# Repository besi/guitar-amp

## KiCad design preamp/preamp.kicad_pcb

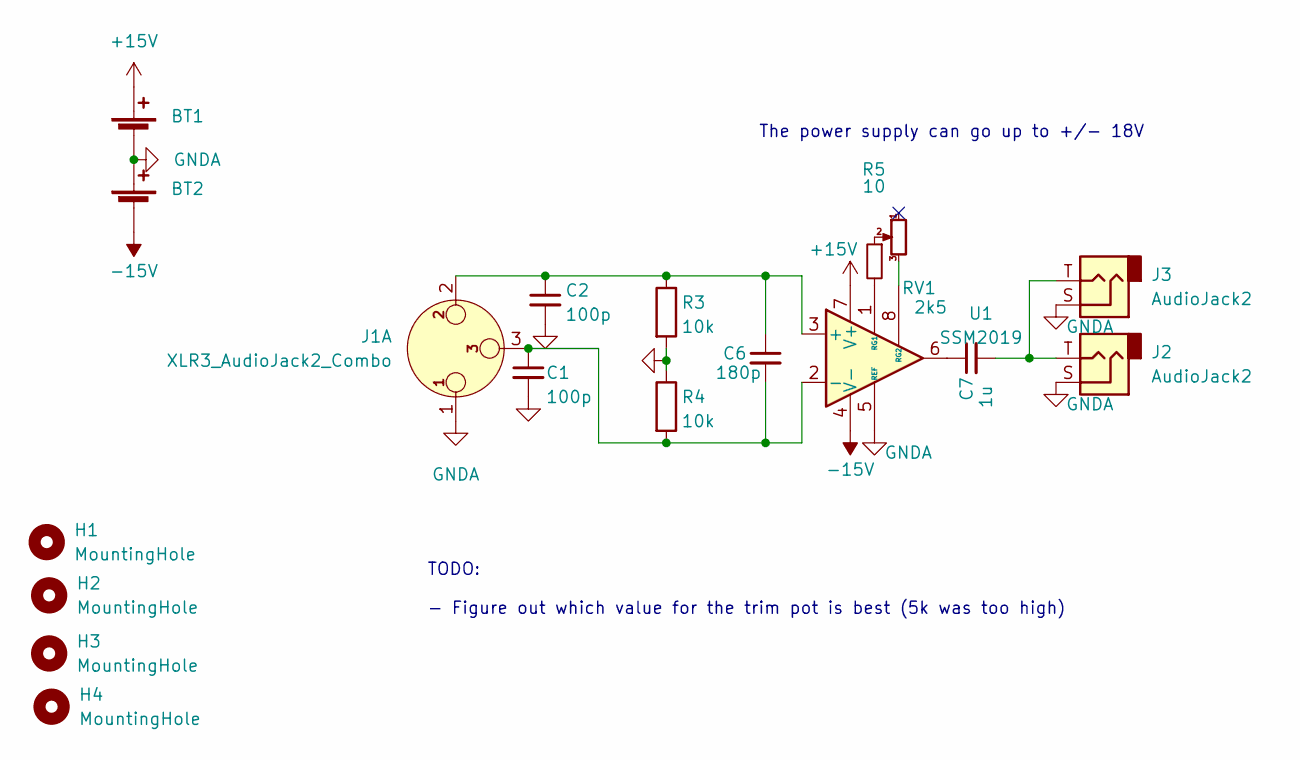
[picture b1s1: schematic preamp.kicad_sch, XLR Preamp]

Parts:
BT1, BT2: Battery_Cell; BarrelJack_GCT_DCJ200-10-A_Horizontal
C1, C2: 100p; C_Disc_D3.0mm_W1.6mm_P2.50mm
C6: 180p; C_Disc_D3.0mm_W1.6mm_P2.50mm
C7: 1u; C_Rect_L7.0mm_W2.5mm_P5.00mm
H1, H2, H3, H4: MountingHole; MountingHole_3.2mm_M3_DIN965
J1: XLR3_AudioJack2_Combo; Jack_XLR_Neutrik_NC3FAAH2_Horizontal
J2: AudioJack2; Jack_6.35mm_Neutrik_NMJ6HFD2_Horizontal
J3: AudioJack2; Jack_3.5mm_CUI_SJ-3523-SMT_Horizontal
R3, R4: 10k; R_Axial_DIN0207_L6.3mm_D2.5mm_P7.62mm_Horizontal
R5: 10; R_Axial_DIN0207_L6.3mm_D2.5mm_P7.62mm_Horizontal
RV1: 2k5; Potentiometer_Alps_RK163_Single_Horizontal
U1: SSM2019; DIP-8_W7.62mm_LongPads

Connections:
+15V: BT1.1 (+), U1.7 (V+)
-15V: BT2.2 (-), U1.4 (V-)
GNDA: BT1.2 (-), BT2.1 (+), C1.2, C2.2, J1.1, J2.S, J3.S, R3.2, R4.1, U1.5 (REF)
unnamed: C1.1, C6.2, J1.3, R4.2, U1.2 (-)
unnamed: C2.1, C6.1, J1.2, R3.1, U1.3 (+)
unnamed: C7.1, U1.6
unnamed: C7.2, J2.T, J3.T
unnamed: R5.1, RV1.2
unnamed: R5.2, U1.1 (RG1)
unnamed: RV1.3, U1.8 (RG2)

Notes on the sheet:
The power supply can go up to +/- 18V
TODO: - Figure out which value for the trim pot is best (5k was too high)

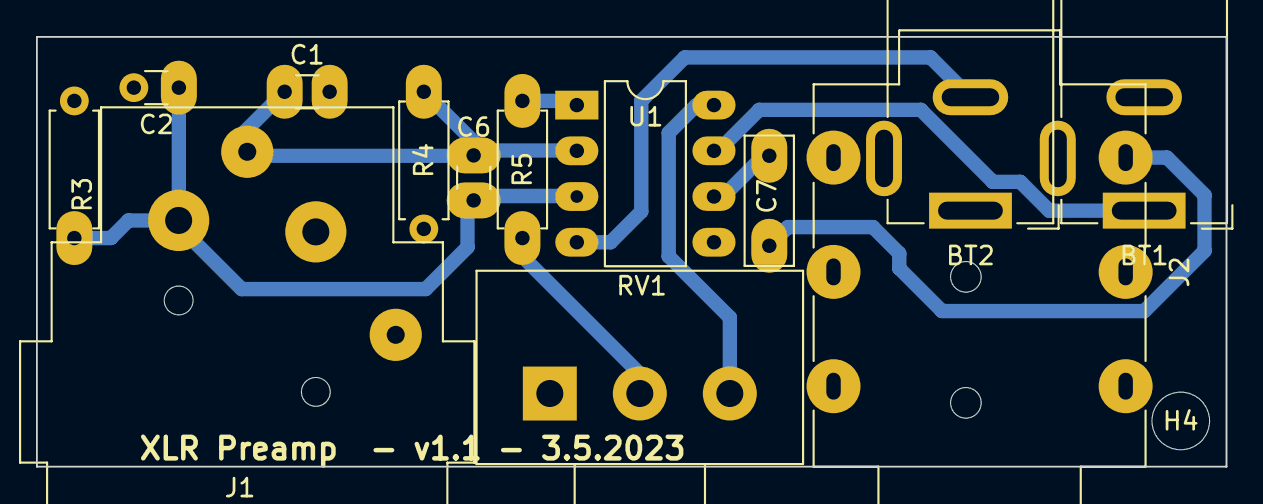
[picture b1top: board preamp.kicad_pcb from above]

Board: 2 copper layers, 66.1 x 23.9 mm, 18 parts (1 on the bottom side), 10 nets.

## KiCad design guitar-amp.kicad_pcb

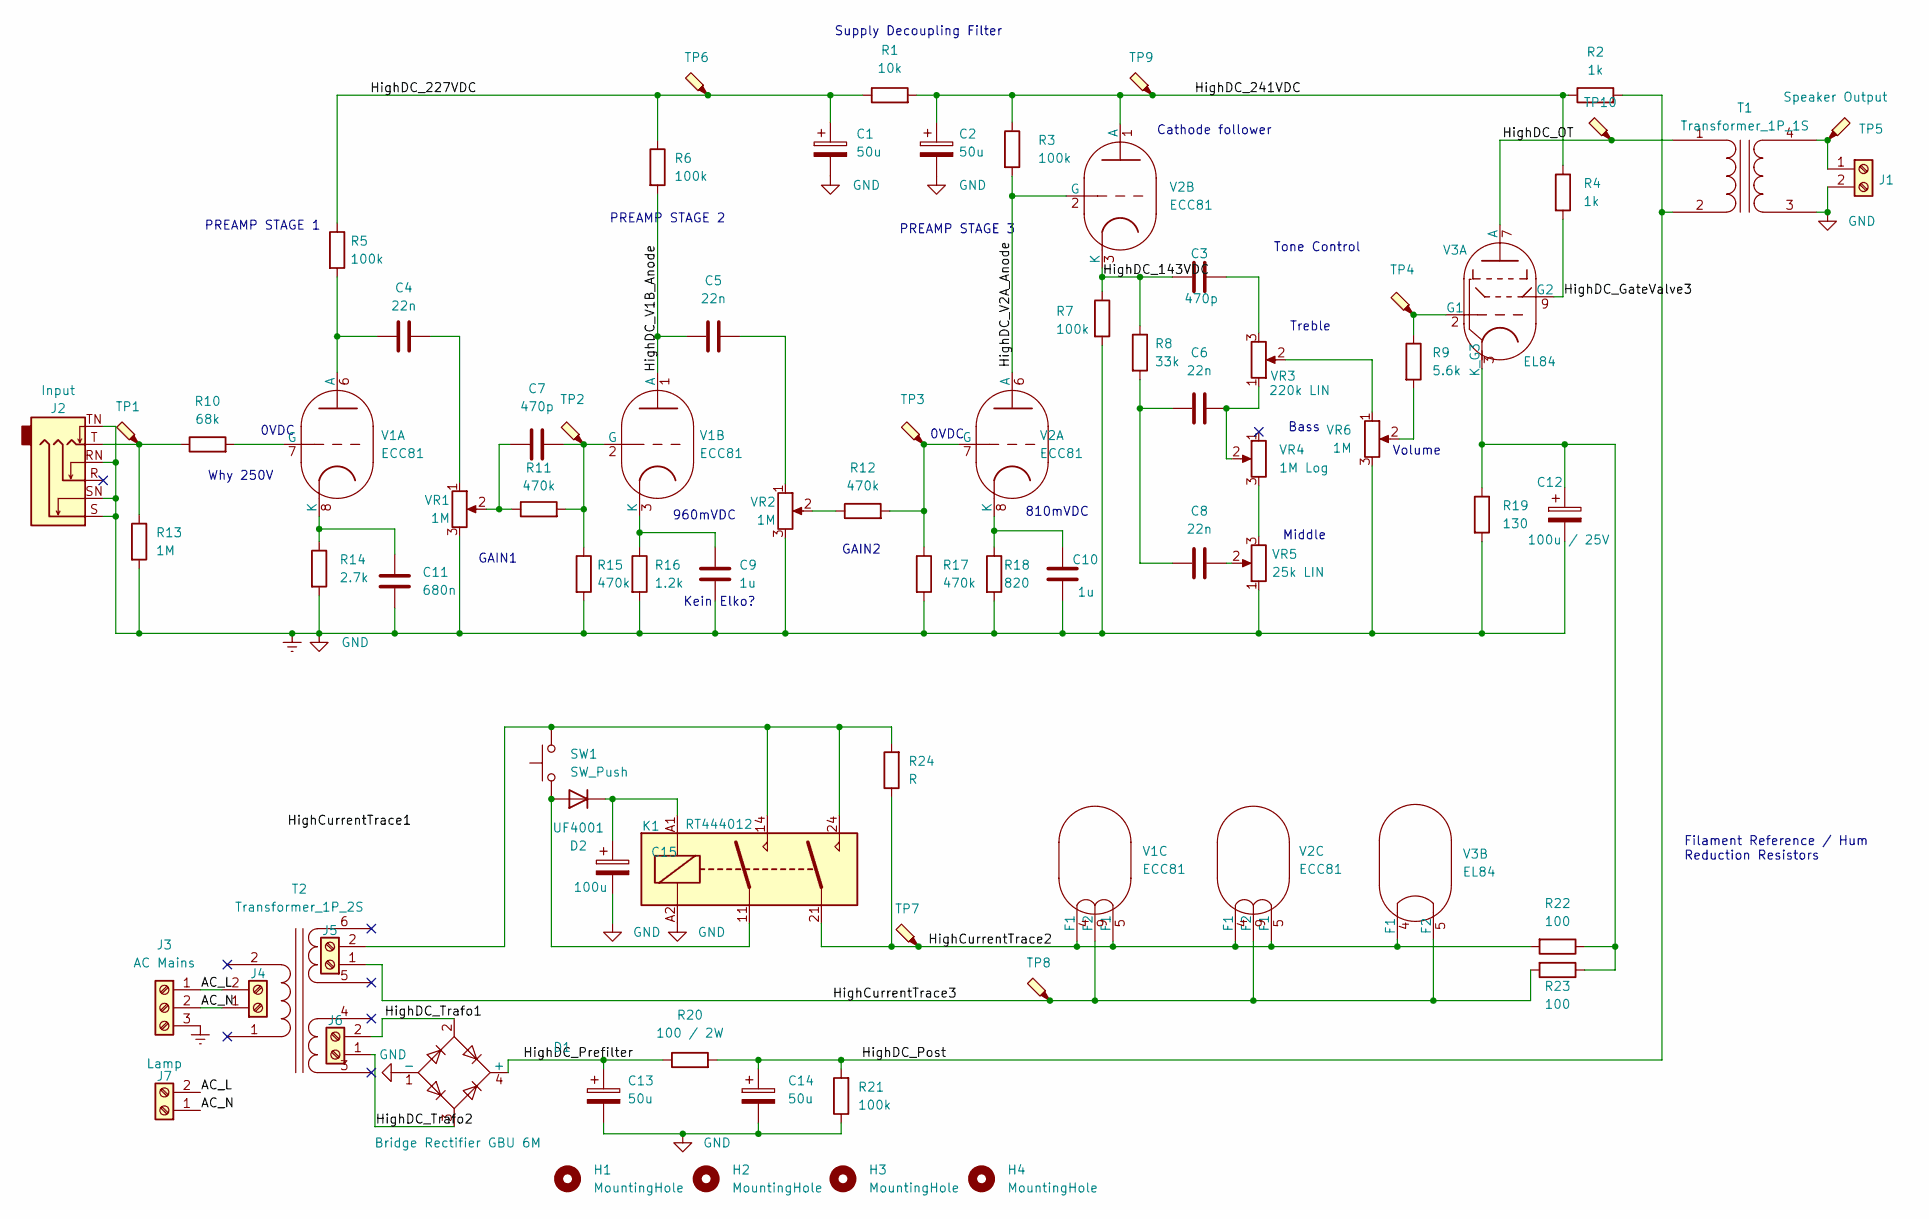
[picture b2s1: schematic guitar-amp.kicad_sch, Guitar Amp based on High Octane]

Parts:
C1, C2, C13, C14: 50u; CP_Radial_D16.0mm_P7.50mm
C3, C7: 470p; C_Disc_D7.0mm_W2.5mm_P5.00mm
C4, C5, C6, C8: 22n; C_Rect_L18.0mm_W5.0mm_P15.00mm_FKS3_FKP3
C9, C10: 1u; C_Rect_L10.3mm_W5.0mm_P7.50mm_MKS4
C11: 680n; C_Axial_L17.0mm_D7.0mm_P20.00mm_Horizontal
C12: 100u / 25V; CP_Radial_D8.0mm_P3.80mm
C15: 100u
D1: Bridge Rectifier GBU 6M; Diode_Bridge_Vishay_GBU
D2: UF4001; D_DO-41_SOD81_P10.16mm_Horizontal
H1, H2, H3, H4: MountingHole; MountingHole_3.2mm_M3
J1: Speaker Output; TerminalBlock_RND_205-00001_1x02_P5.00mm_Horizontal
J2: Input; Jack_6.35mm_Neutrik_NMJ6HFD2-AU_Horizontal
J3: AC Mains; TerminalBlock_RND_205-00002_1x03_P5.00mm_Horizontal
J4, J5, J6: Screw_Terminal_01x02; TerminalBlock_RND_205-00001_1x02_P5.00mm_Horizontal
J7: Lamp; TerminalBlock_RND_205-00001_1x02_P5.00mm_Horizontal
K1: RT444012; Relay_DPST_Schrack-RT2-FormA_RM5mm
R1: 10k; R_Axial_DIN0411_L9.9mm_D3.6mm_P12.70mm_Horizontal
R2, R4: 1k; R_Axial_DIN0411_L9.9mm_D3.6mm_P12.70mm_Horizontal
R3, R5, R6, R7: 100k; R_Axial_DIN0207_L6.3mm_D2.5mm_P7.62mm_Horizontal
R8: 33k; R_Axial_DIN0207_L6.3mm_D2.5mm_P7.62mm_Horizontal
R9: 5.6k; R_Axial_DIN0207_L6.3mm_D2.5mm_P7.62mm_Horizontal
R10: 68k; R_Axial_DIN0207_L6.3mm_D2.5mm_P7.62mm_Horizontal
R11, R12, R15, R17: 470k; R_Axial_DIN0207_L6.3mm_D2.5mm_P7.62mm_Horizontal
R13: 1M; R_Axial_DIN0207_L6.3mm_D2.5mm_P7.62mm_Horizontal
R14: 2.7k; R_Axial_DIN0207_L6.3mm_D2.5mm_P7.62mm_Horizontal
R16: 1.2k; R_Axial_DIN0207_L6.3mm_D2.5mm_P7.62mm_Horizontal
R18: 820; R_Axial_DIN0207_L6.3mm_D2.5mm_P7.62mm_Horizontal
R19: 130; R_Axial_DIN0411_L9.9mm_D3.6mm_P12.70mm_Horizontal
R20: 100 / 2W; R_Axial_DIN0411_L9.9mm_D3.6mm_P12.70mm_Horizontal
R21: 100k; R_Axial_DIN0411_L9.9mm_D3.6mm_P12.70mm_Horizontal
R22, R23: 100; R_Axial_DIN0207_L6.3mm_D2.5mm_P7.62mm_Horizontal
R24: R; R_Axial_Power_L20.0mm_W6.4mm_P25.40mm
SW1: SW_Push; SW_Tactile_SPST_Angled_PTS645Vx58-2LFS
T1: Transformer_1P_1S; TerminalBlock_RND_205-00003_1x04_P5.00mm_Horizontal
T2: Transformer_1P_2S
TP1, TP2, TP3, TP4, TP5, TP6, TP7, TP8, TP9, TP10: TestPoint_Probe; TestPoint_Pad_D2.5mm
V1, V2: ECC81; Valve_ECC-83-1
V3: EL84; Valve_ECC-83-1
VR1, VR2, VR6: 1M; Potentiometer_Alps_RK163_Single_Horizontal
VR3: 220k LIN; Potentiometer_Alps_RK163_Single_Horizontal
VR4: 1M Log; Potentiometer_Alps_RK163_Single_Horizontal
VR5: 25k LIN; Potentiometer_Alps_RK163_Single_Horizontal

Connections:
/AC_L: J3.1, J4.2, J7.2
/AC_N: J3.2, J4.1, J7.1
/HighCurrentTrace2: K1.21, R22.2, R24.1, TP7.1, V1.4 (F1), V1.5 (F1), V2.4 (F1), V2.5 (F1), V3.4 (F1)
/HighCurrentTrace3: J5.1, R23.2, TP8.1, V1.9 (F2), V2.9 (F2), V3.5 (F2)
/HighDC_143VDC: C3.1, R7.1, R8.1, V2.3 (K)
/HighDC_227VDC: C1.1, R1.1, R5.1, R6.1, TP6.1
/HighDC_241VDC: C2.1, R1.2, R2.1, R3.1, R4.1, TP9.1, V2.1 (A)
/HighDC_GateValve3: R4.2, V3.9 (G2)
/HighDC_OT: T1.1 (AA), TP10.1, V3.7 (A)
/HighDC_Post: C14.1, R2.2, R20.2, R21.2, T1.2 (AB)
/HighDC_Prefilter: C13.1, D1.4 (+), R20.1
/HighDC_Trafo1: D1.2, J6.2
/HighDC_Trafo2: D1.3, J6.1
/HighDC_V1B_Anode: C5.1, R6.2, V1.1 (A)
/HighDC_V2A_Anode: R3.2, V2.2 (G), V2.6 (A)
Earth: C1.2, C2.2, C9.2, C10.2, C11.2, C12.2, C13.2, C14.2, C15.2, D1.1 (-), J1.2, J2.RN, J2.S, J2.SN, J2.TN, J3.3, K1.A2, R7.2, R13.2, R14.2, R15.2, R16.2, R17.2, R18.2, R19.2, R21.1, T1.3 (SA), VR1.3, VR2.3, VR5.1, VR6.3
unnamed: C3.2, VR3.3
unnamed: C4.1, R5.2, V1.6 (A)
unnamed: C4.2, VR1.1
unnamed: C5.2, VR2.1
unnamed: C6.1, C8.1, R8.2
unnamed: C6.2, VR3.1, VR4.2
unnamed: C7.1, R11.1, VR1.2
unnamed: C7.2, R11.2, R15.1, TP2.1, V1.2 (G)
unnamed: C8.2, VR5.2
unnamed: C9.1, R16.1, V1.3 (K)
unnamed: C10.1, R18.1, V2.8 (K)
unnamed: C11.1, R14.1, V1.8 (K)
unnamed: C12.1, R19.1, R22.1, R23.1, V3.3 (K_G3)
unnamed: J1.1, T1.4 (SB), TP5.1
unnamed: J2.T, R10.1, R13.1, TP1.1
unnamed: J5.2, K1.14, K1.24, R24.2, SW1.2
unnamed: D2.2 (A), K1.11, SW1.1
unnamed: C15.1, D2.1 (K), K1.A1
unnamed: R9.1, TP4.1, V3.2 (G1)
unnamed: R9.2, VR6.2
unnamed: R10.2, V1.7 (G)
unnamed: R12.1, VR2.2
unnamed: R12.2, R17.1, TP3.1, V2.7 (G)
unnamed: VR3.2, VR6.1
unnamed: VR4.3, VR5.3

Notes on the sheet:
960mVDC
Cathode follower
Why 250V
PREAMP STAGE 1
Volume
Treble
Filament Reference / Hum Reduction Resistors
0VDC
810mVDC
Kein Elko?
GAIN1
GAIN2
PREAMP STAGE 3
PREAMP STAGE 2
Middle
Supply Decoupling Filter
Bass
Tone Control

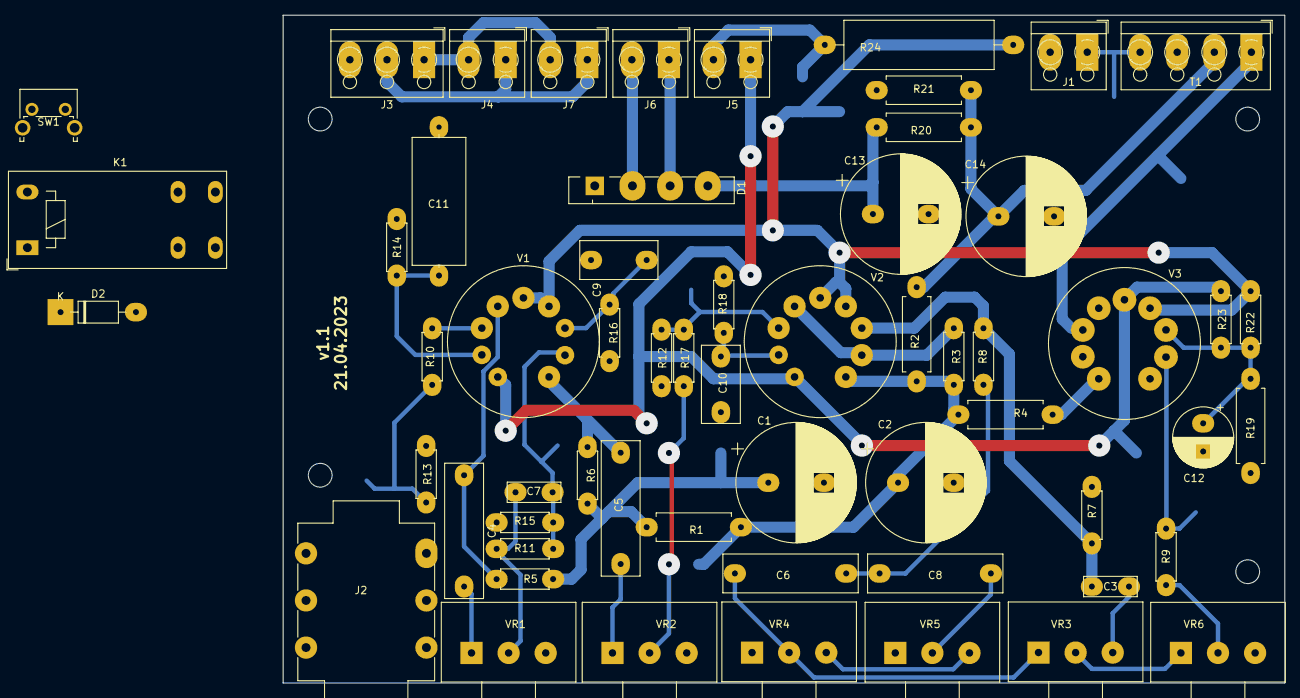
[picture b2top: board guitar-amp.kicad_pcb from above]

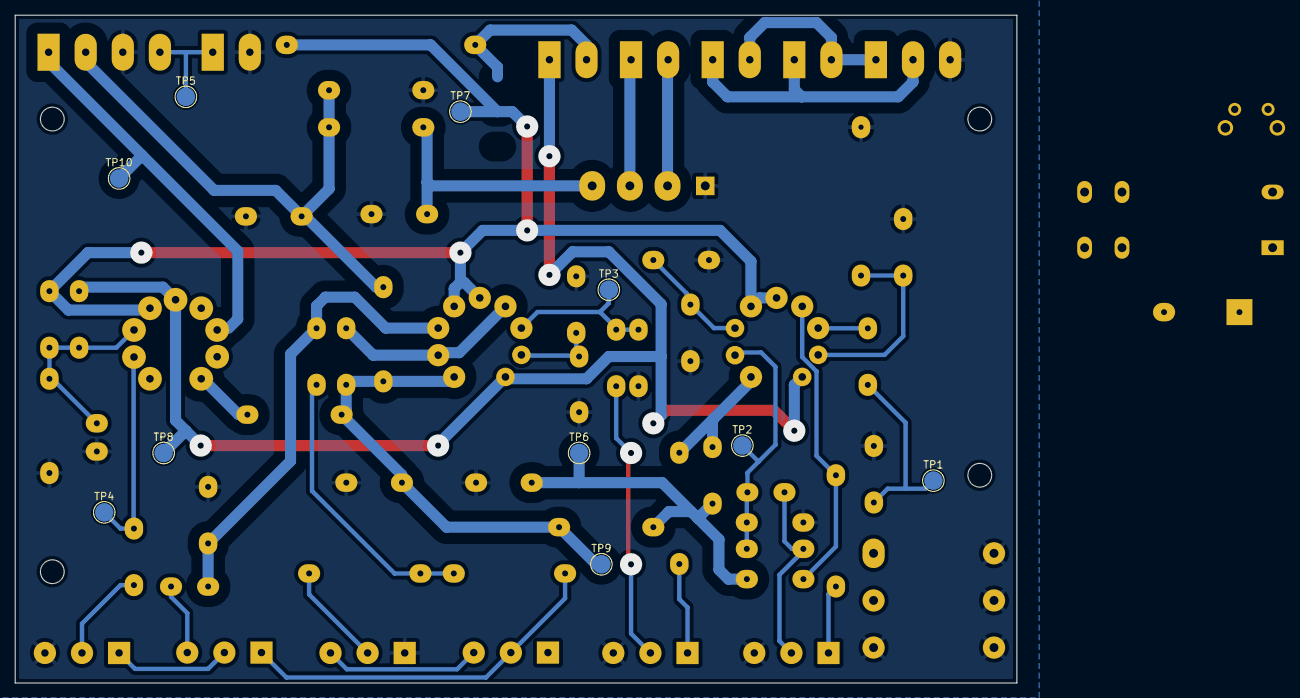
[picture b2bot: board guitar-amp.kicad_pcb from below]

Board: 2 copper layers, 135.0 x 90.0 mm, 73 parts (10 on the bottom side), 41 nets.

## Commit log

2023-02-19 Added empty project
2023-03-10 Add valves
2023-04-04 Add resistors
2023-04-04 Add capacitors
2023-04-04 Add potentiometers
2023-04-11 Add guitar jack
2023-04-11 Model the schematic
2023-04-12 Roughly layout the components on the PCB
2023-04-12 First draft of routing
2023-04-16 Routing improvements
2023-04-16 update pads
2023-04-16 Update version
2023-04-16 prepare for plotting
2023-04-21 Add lamp and test points
2023-04-21 Make the filament traces bigger
2023-04-21 Integrate feedback from stackoverflow
2023-04-24 Fix R6 and Remove C15
2023-04-24 Self latching circuit for soft start
2023-04-29 Add preamp for mic
2023-04-29 Prepare for routing
2023-04-30 Add RCA Plug
2023-04-30 Routing of preamp
2023-04-30 Add 3d models
2023-05-01 Add mounting holes
2023-05-01 Prepare for milling
2023-05-02 Update board with the findings of the pcb
2023-05-05 Replace the RCA jack with an Audio Jack
2023-05-05 milling
2023-05-06 Small improvements
2023-05-06 Cleanup
2023-05-06 Small changes
